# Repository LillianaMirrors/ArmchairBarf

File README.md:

# ArmchairBarf

Armchair Barf is a simple little project to get myself warmed up to PCB design. It uses the same form factor as WhoppingPochard / VinnyC's rather popular "Rainbow Barf"

I will openly warn: The design is not tested in reality. Build at your own risk.

The PCB is designed to be easy access, with the AE lit up first, and then the middle ribbon with the last 3 neopixels.

For the rear pins, the square will be Data In/Out, GND in the middle, and +5v on the opposing side.

J1 is Data In, J2 is Data Out.

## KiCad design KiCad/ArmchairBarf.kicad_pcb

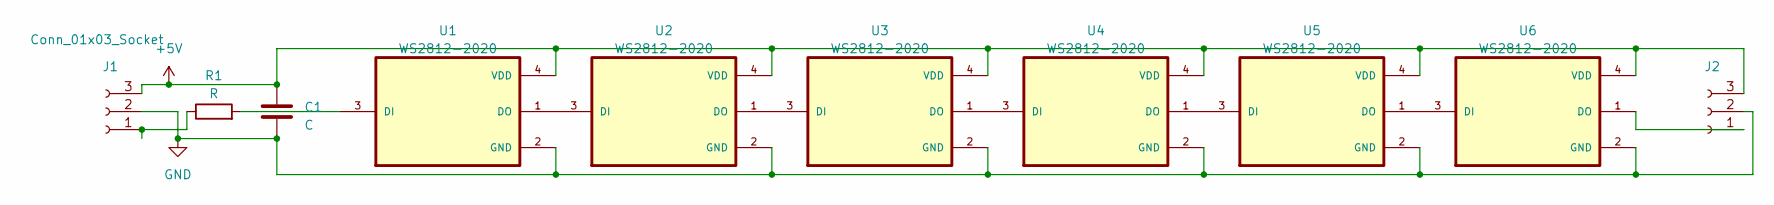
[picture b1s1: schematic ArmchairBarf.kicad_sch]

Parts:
C1: C; C_0402_1005Metric
J1, J2: Conn_01x03_Socket; SolderWire-0.1sqmm_1x03_P3.6mm_D0.4mm_OD1mm
R1: R; R_0402_1005Metric
U1, U2, U3, U4, U5, U6: WS2812-2020; LED_WS2812-2020; PARTREV V1.3

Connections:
+5V: C1.1, J1.3, J2.3, U1.4 (VDD), U2.4 (VDD), U3.4 (VDD), U4.4 (VDD), U5.4 (VDD), U6.4 (VDD)
GND: C1.2, J1.2, J2.2, U1.2 (GND), U2.2 (GND), U3.2 (GND), U4.2 (GND), U5.2 (GND), U6.2 (GND)
unnamed: J1.1, R1.1
unnamed: J2.1, U6.1 (DO)
unnamed: R1.2, U1.3 (DI)
unnamed: U1.1 (DO), U2.3 (DI)
unnamed: U2.1 (DO), U3.3 (DI)
unnamed: U3.1 (DO), U4.3 (DI)
unnamed: U4.1 (DO), U5.3 (DI)
unnamed: U5.1 (DO), U6.3 (DI)

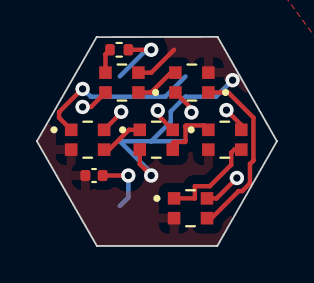
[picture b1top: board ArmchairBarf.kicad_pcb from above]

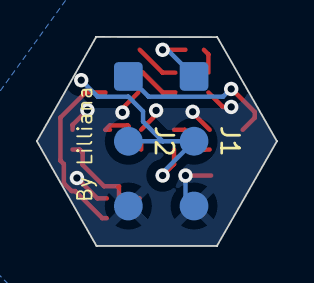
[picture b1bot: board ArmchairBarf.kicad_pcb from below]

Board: 2 copper layers, 13.3 x 11.6 mm, 10 parts (2 on the bottom side), 10 nets.

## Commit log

2023-06-02 Cleaned up and made proper connections and repinned to hartk's suggestions
2023-06-05 Redesigned for Whopping's Rainbow Barf form factor.
2023-06-07 V1 release!
2023-06-07 Cleanup of V1
2023-06-07 v1 logs
